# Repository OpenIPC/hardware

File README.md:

![OpenIPC logo][logo]

## OpenIPC hardware developments 

[][telegram]

### A collection of hardware developments by the OpenIPC team

- [One of the open board for OpenIPC](board_hi3516ev200)
- [8812AU module dock board for camera,input 6V@2A max and 28V@ 3A max](/module_38x38_r8812au_6v2a)
- [WIFI board for stacking on 20mm square hole flight controller for FPV](WIFI-BOARD)

### A collection of 3D models for use in OpenIPC projects

- [OpenIPC models on Printables site](https://www.printables.com/search/models?q=tag:openipc)
- [5 inch racer drone equipped with OpenIPC](OpenIPC-5inchRacer)

### Measure the output of RTL8812AU.
- [Measure the output of RTL8812AU](spectram)

More information about the [project][project] is available in our [website][website]
and on the [wiki][wiki].

<p align="center">

</p>

[firmware]: https://github.com/openipc/firmware/
[logo]: https://openipc.org/assets/openipc-logo-black.svg
[mit]: https://opensource.org/license/mit/
[opencollective]: https://opencollective.com/openipc
[paypal]: https://www.paypal.com/donate/?hosted_button_id=C6F7UJLA58MBS
[project]: https://github.com/openipc/
[telegram]: https://t.me/OpenIPC
[website]: https://openipc.org/
[wiki]: https://github.com/openipc/wiki/

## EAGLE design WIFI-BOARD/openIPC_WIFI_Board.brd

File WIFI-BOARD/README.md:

## WIFI board for stacking on 20mm square hole flight controller for FPV
### *.f3z: EAGLE file for FUSUION360
### *.sch: Schematic file for EAGLE
### *.brd: Board file for EAGLE
### *.zip: Gerber data for sending to the board manufacturing company that includes this board as a set of 4

### HOW TO USE
Prepare a standoff of this shape

Attach it to the flight controller installation screw like this

Install this WIFI module on it.

<p align="center">

</p>

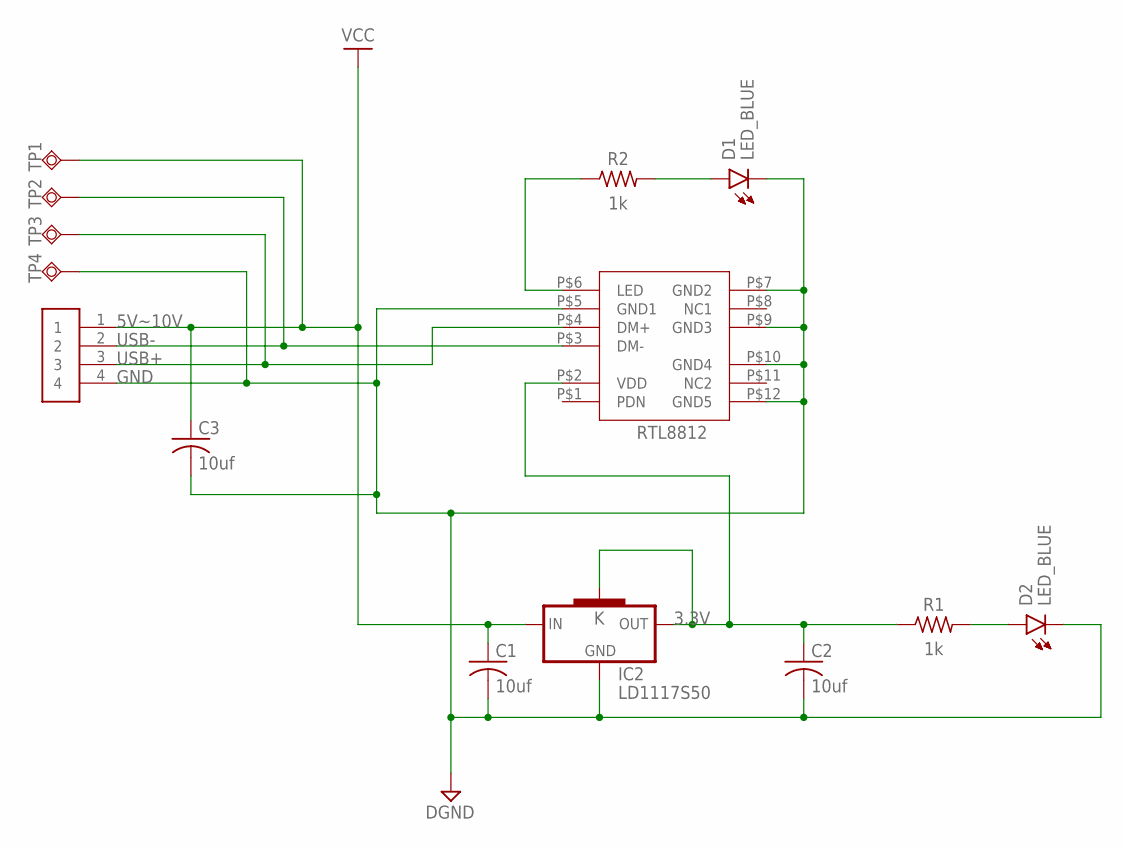
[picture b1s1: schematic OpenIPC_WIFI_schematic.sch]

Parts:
C1, C2, C3: 10uf; CAPC1608X85
D1, D2: LED_BLUE; LEDC1608X35N_FLAT-B
IC2: LD1117S50; SOT223
R1, R2: 1k; RESC1608X60
TP1, TP2, TP3, TP4: TPSQTP16SQ; TP16SQ
U$1: RTL8812AU; RTL8812
U$2: JST-GH-4SIDE; JST-GH-SIDE-4

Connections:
DGND: C1.2, C2.2, C3.2, D1.C, D2.C, IC2.1 (GND), TP4.TP, U$1.P$5 (GND1), U$1.P$7 (GND2), U$1.P$9 (GND3), U$1.P$10 (GND4), U$1.P$12 (GND5), U$2.4
unnamed: R2.1, U$1.P$6 (LED)
unnamed: TP2.TP, U$1.P$3 (DM-), U$2.2
unnamed: TP3.TP, U$1.P$4 (DM+), U$2.3
unnamed: D1.A, R2.2
unnamed: C2.1, IC2.2 (OUT), IC2.4 (K), R1.1, U$1.P$2 (VDD)
unnamed: D2.A, R1.2
VCC: C1.1, C3.1, IC2.3 (IN), TP1.TP, U$2.1

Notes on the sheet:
5V~10V
USB-
USB+
GND
3.3V

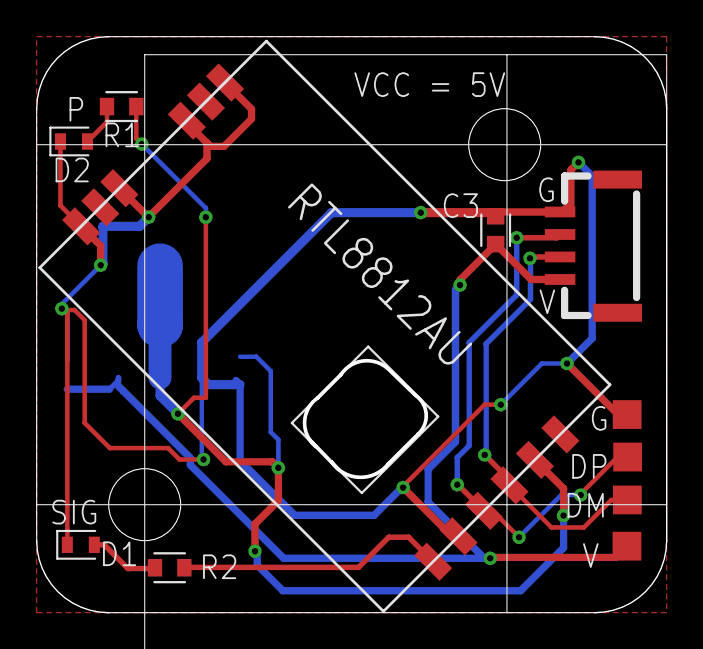
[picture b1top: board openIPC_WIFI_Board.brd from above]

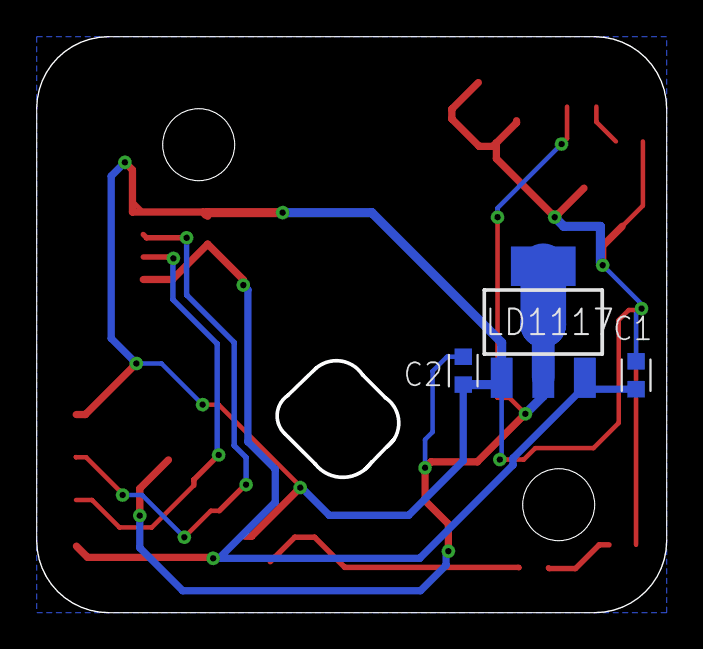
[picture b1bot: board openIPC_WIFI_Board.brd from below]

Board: 2 copper layers, 35.0 x 32.0 mm, 14 parts (3 on the bottom side), 8 nets.

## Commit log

2023-10-23 Add module_38x38_r8812au_6v2a
2023-10-23 Add board_hi3516ev200
2023-10-24 upgrade board logo
2023-10-24 28V maxinput For R8812AU 38mmx38mm board
    2S-4S lipro use
2023-10-24 Update Readme.md
    Add 28V version
2023-10-25 update board logo and Readme
2023-10-25 updates
    new cover for rtl8812au 150mw module with hole for heatsink
2023-10-25 Update README.md
    add photo cover2.stl
2023-10-27 add 28V board and connection reference
2023-10-27 Add connection reference for 28V dock board
2023-10-28 VRX models
2023-10-28 Delete hi3536_box_3d-model directory
    The project has moved to the Printables website
    https://www.printables.com/search/models?q=tag:openipc
2023-11-01 NVR board 3D model for OpenIPC
2023-11-01 3D model picture for NVR board
2023-11-14 add flash type convert for camhi and anjoy
2024-09-28 Add a whoop-size BL-R8812AF1 mount PCB
2024-10-12 Adding my double-WiFi, Radxa-stackable USB hub PCB
2024-10-12 Fixing readme
2024-10-12 Fix readme 2
2024-10-12 Fix readme 3
2024-10-12 Fix readme 4
2024-10-12 Fix readme 5
2024-10-12 Adding my double WiFi, Radxa-stackable USB hub PCB
2024-10-29 Update README.md
    Add warning about problems with the board.
